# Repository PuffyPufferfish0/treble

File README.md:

# ESP32 I2S Audio Player -Treble

A hardware-based audio player built around the ESP32, utilizing a PCM5102A DAC for high-quality I2S digital audio output, a MicroSD card reader for storage, and an analog joystick for intuitive control.

## Features
* **High-Fidelity Audio:** Hardware-decoded streaming via the PCM5102A DAC over the I2S bus.
* **Expandable Storage:** Reads audio files (e.g., 8MB `.mp3` streams) directly from a MicroSD card via SPI.
* **Analog Navigation:** KY-023 joystick integration for track/menu navigation, paired with a dedicated momentary trigger button.
* **Custom PCB:** Designed in KiCad to transition from a breadboard prototype to a clean, modular printed circuit board.

## Hardware Components
* ESP32-DevKitC
* PCM5102A I2S DAC Module *(Note: XSMT pin physically bridged to HIGH for hardware unmuting)*
* MicroSD Card Adapter
* KY-023 Analog Joystick
* Momentary Push Button

## Pin Mapping

| Component | Pin | ESP32 GPIO | Notes |
| :--- | :--- | :--- | :--- |
| **PCM5102A DAC** | BCK | GPIO 26 | I2S Bit Clock |
| | DIN | GPIO 22 | I2S Data In |
| | LCK | GPIO 25 | I2S Word Select |
| | SCK | GPIO 13 | Driven LOW in software |
| **MicroSD Reader**| MISO | GPIO 19 | VSPI Bus |
| | MOSI | GPIO 23 | VSPI Bus |
| | CLK | GPIO 18 | VSPI Bus |
| | CS | GPIO 5 | VSPI Bus |
| **KY-023 Joystick**| VRX | GPIO 32 | Analog Input (Powered via 3.3V) |
| | VRY | GPIO 33 | Analog Input (Powered via 3.3V) |
| **Trigger Button** | Pin 1 | GPIO 27 | Requires `INPUT_PULLUP` |\
## WARNING
this project *is* still in development 

## Software & Dependencies
This project is built using the Arduino IDE/PlatformIO for the ESP32.
* [ESP32-audioI2S](https://github.com/schreibfaul1/ESP32-audioI2S) - Core library for I2S output and MP3 decoding.
* Standard `SPI.h` and `SD.h` libraries for file system management.

- [x] Breadboard prototyping and hardware debugging
- [x] Hardware mute-bypass modification on DAC
- [x] Schematic in KiCad
- [x] PCB layout and routing
- [ ] Custom PCB fabrication and assembly

# trebleIDE

An Electron application with React

## Recommended IDE Setup

- [VSCode](https://code.visualstudio.com/) + [ESLint](https://marketplace.visualstudio.com/items?itemName=dbaeumer.vscode-eslint) + [Prettier](https://marketplace.visualstudio.com/items?itemName=esbenp.prettier-vscode)

## Project Setup

### Install

```bash
$ npm install
```

### Development

```bash
$ npm run dev
```

### Build

```bash
# For windows
$ npm run build:win

# For macOS
$ npm run build:mac

# For Linux
$ npm run build:linux
```

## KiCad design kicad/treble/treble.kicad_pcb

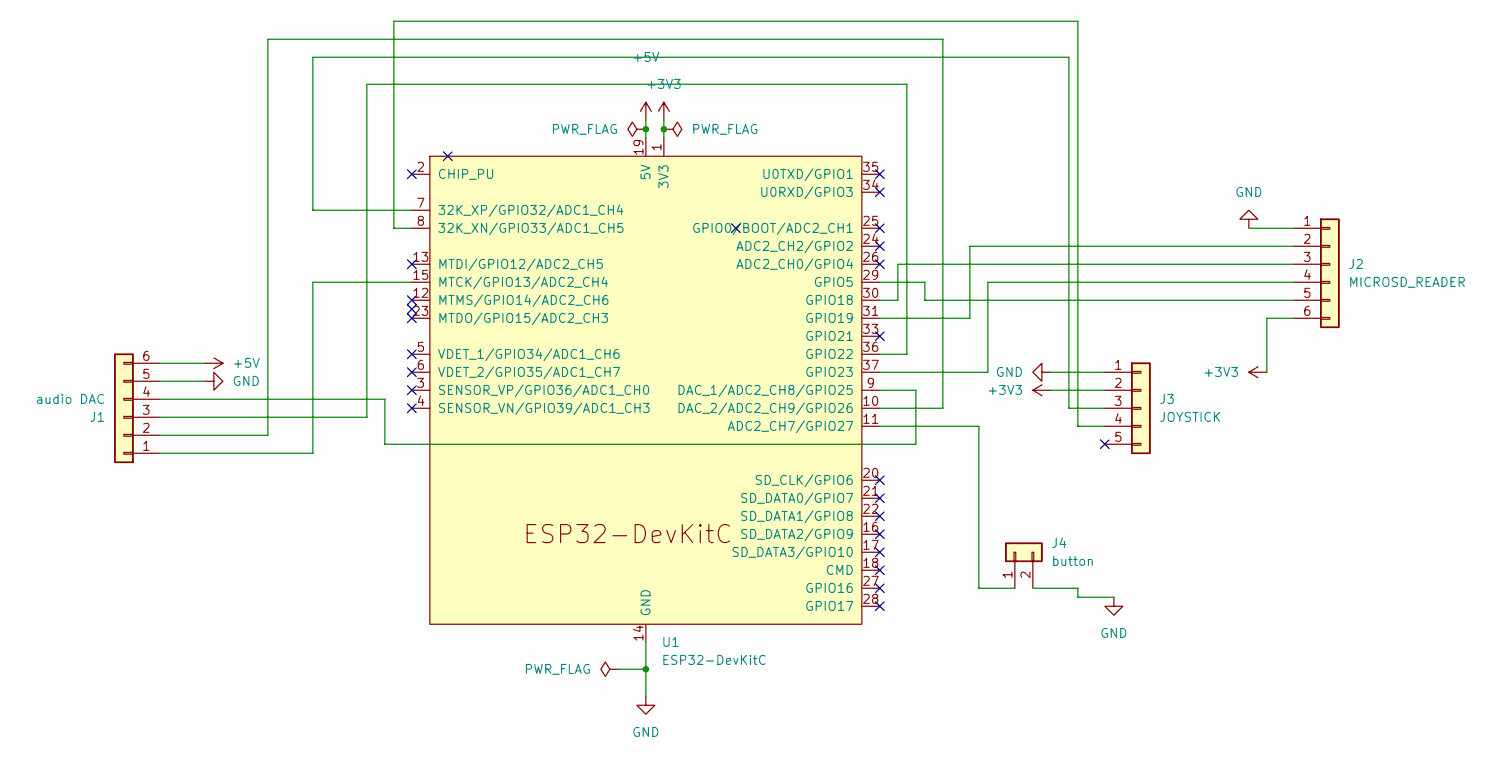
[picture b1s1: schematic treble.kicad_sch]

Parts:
J1: audio DAC; PinHeader_1x06_P2.54mm_Horizontal
J2: MICROSD_READER; PinHeader_1x06_P2.54mm_Horizontal
J3: JOYSTICK; PinHeader_1x05_P2.54mm_Vertical_SMD_Pin1Right
J4: button; PinHeader_1x02_P2.54mm_Horizontal
U1: ESP32-DevKitC

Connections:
+3V3: J2.6 (3V3), J3.2 (+5v(3.3V)), U1.1 (3V3)
+5V: J1.6 (VIN), U1.19 (5V)
GND: J1.5 (GND), J2.1 (GND), J3.1 (GND), J4.2, U1.14 (GND), U1.32 (GND), U1.38 (GND)
unnamed: J1.2 (BCK), U1.10 (DAC_2/ADC2_CH9/GPIO26)
unnamed: J1.3 (DIN), U1.36 (GPIO22)
unnamed: J1.4 (LCK), U1.9 (DAC_1/ADC2_CH8/GPIO25)
unnamed: J1.1 (SCK), U1.15 (MTCK/GPIO13/ADC2_CH4)
unnamed: J2.3 (CLK), U1.30 (GPIO18)
unnamed: J2.5 (CS), U1.29 (GPIO5)
unnamed: J2.2 (MISO), U1.31 (GPIO19)
unnamed: J2.4 (MOSI), U1.37 (GPIO23)
unnamed: J3.3 (VRX), U1.7 (32K_XP/GPIO32/ADC1_CH4)
unnamed: J3.4 (VRY), U1.8 (32K_XN/GPIO33/ADC1_CH5)
unnamed: J4.1, U1.11 (ADC2_CH7/GPIO27)

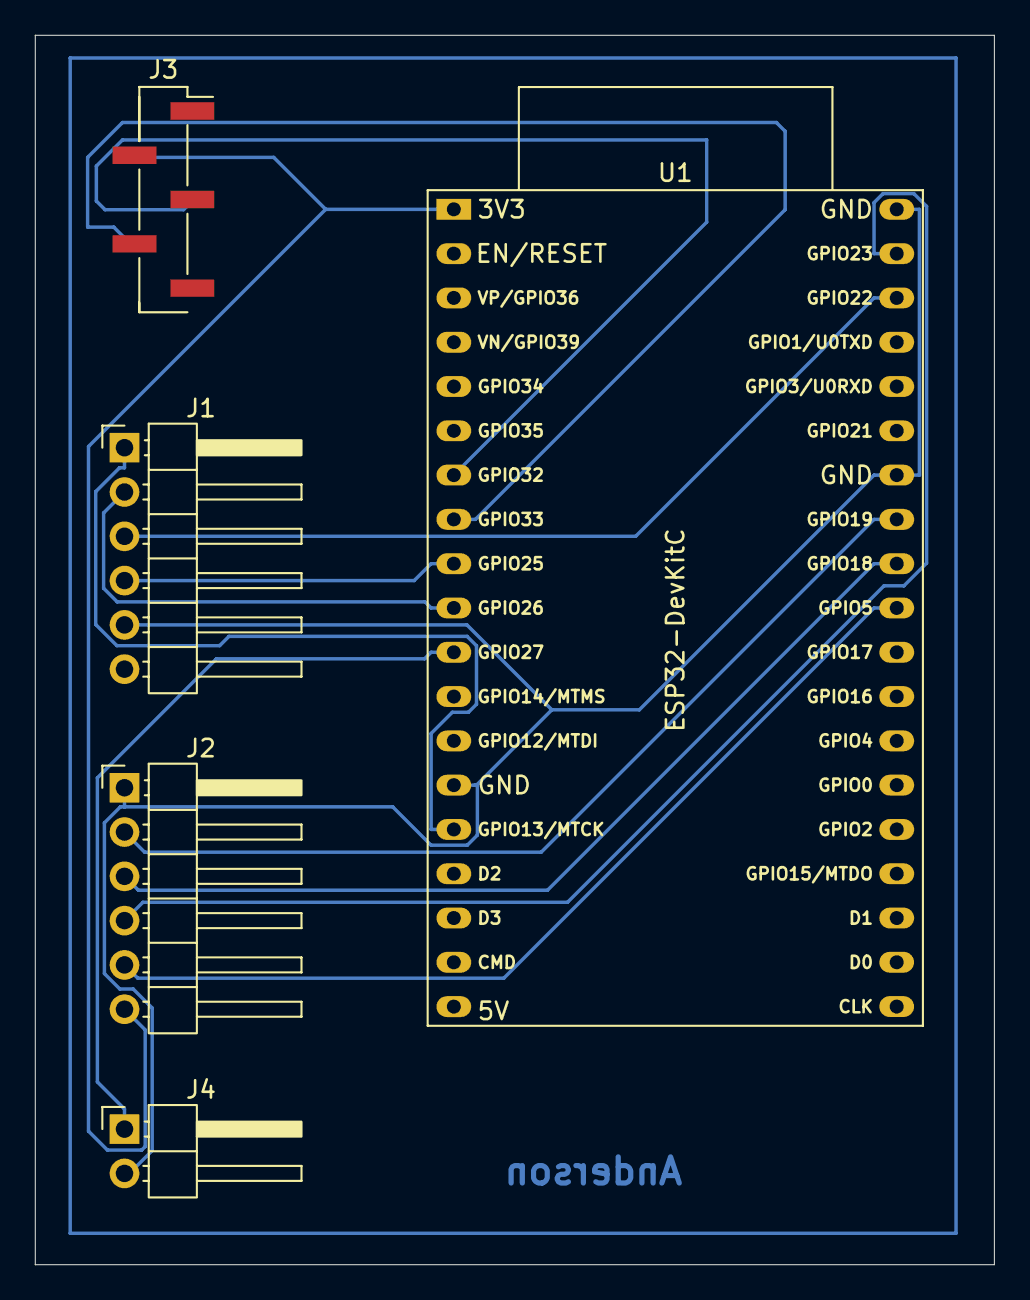
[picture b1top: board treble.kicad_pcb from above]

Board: 2 copper layers, 55.0 x 70.5 mm, 5 parts (0 on the bottom side), 14 nets.

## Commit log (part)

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2026-05-28 setup electron-vite and made a simple demo IDE
